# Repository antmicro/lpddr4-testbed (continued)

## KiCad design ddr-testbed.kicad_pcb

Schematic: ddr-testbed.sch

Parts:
C1, C5, C40, C41, C42: C_10u_0402; 0402-cap; MPN GRM155R60J106ME44D
C2: C_3p3_0402; 0402-res; MPN C0402C339C5GACAUTO
C3: C_10n_0402; 0402-cap; MPN 04025G103ZAT2A
C4: C_100n_0402_6V3; 0402-cap; MPN 0402X104K6R3CT
C6, C7, C44, C46, C48, C50: C_1u_0201; 0201-res; MPN CC0201KRX5R5BB105
C8, C9, C10, C11, C12, C13, C14, C15, C16, C17, C18, C19, C20, C21, C22, C23, C24, C25, C26, C27, C28, C29, C30, C31, C32, C33, C34, C35, C36, C37, C38, C39, C43, C45, C47, C49, C51, C52, C53, C54, C55, C56: C_100n_0201; 0201-res; MPN CC0201KRX6S5BB104
FB1: BLM15PD121SN1D; 0402-res; MPN BLM15PD121SN1D
J1: ddr4-sodimm-edge-connector; SODIMM_DDR4_EDGE
R1: R_240R_0402; 0402-res; MPN ERJ2GEJ241X
R2: R_10k_0402; 0402-res; MPN CRCW040210K0FKEDHP
R4, R5, R11, R12, R27, R28, R29, R31, R36: R_0R_0402; 0402-res; MPN ERJ2GE0R00X
R6, R7, R8, R9, R13, R14, R15, R16, R17, R18, R19, R20, R21, R22, R23, R24, R25, R26, R30, R32, R37: R_40R2_0402; 0402-res; MPN MCWR04X40R2FTL
R10: R_75R_0402; 0402-res; MPN RC0402FR-0775RL
R33, R34: R_80R6_0402; 0402-res; MPN MC00625W0402180R6
R35: R_4k7_0402; 0402-res; MPN ERJ2GEJ472X
U1: MT53E256M16D1; BGA-200_10.0x14.5mm_Layout12x22_P0.80x0.65mm

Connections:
/ACT_N: J1.114
/ALERT_N: J1.116, R37.1
/BA0: J1.150
/BA1: J1.145
/BG0: J1.113
/BG1: J1.115
/CA0_A: J1.144, R13.1, U1.H2 (CA0_A)
/CA0_B: J1.146, R20.1, U1.R2 (CA0_B)
/CA1_A: J1.133, R14.1, U1.J2 (CA1_A)
/CA1_B: J1.120, R21.1, U1.P2 (CA1_B)
/CA2_A: J1.132, R15.1, U1.H9 (CA2_A)
/CA2_B: J1.119, R22.1, U1.R9 (CA2_B)
/CA3_A: J1.131, R16.1, U1.H10 (CA3_A)
/CA3_B: J1.158, R23.1, U1.R10 (CA3_B)
/CA4_A: J1.128, R17.1, U1.H11 (CA4_A)
/CA4_B: J1.151, R24.1, U1.R11 (CA4_B)
/CA5_A: J1.126, R18.1, U1.J11 (CA5_A)
/CA5_B: J1.156, R25.1, U1.P11 (CA5_B)
/CK0_C: C2.1, J1.139, R7.1, U1.J9 (CK_C_A)
/CK0_T: C2.2, J1.137, R6.1, U1.J8 (CK_T_A)
/CK1_C: J1.140, R9.1, R10.2, U1.P9 (CK_C_B)
/CK1_T: J1.138, R8.1, R10.1, U1.P8 (CK_T_B)
/CKE0_A: R19.1, U1.J4 (CKE0_A)
/CKE0_B: R26.1, U1.P4 (CKE0_B)
/CKE_0: J1.109, R11.2, R31.1, R34.2
/CKE_0_A: R11.1
/CKE_0_B: R12.1
/CKE_1: J1.110, R12.2, R31.2, R33.2
/CS0_N: J1.149
/CS0_N_A: R4.1, U1.H4 (CS0_A)
/CS0_N_B: R5.1, U1.R4 (CS0_B)
/CS_0_N: R4.2, R27.1, R30.1
/CS_1_N: J1.157, R5.2, R27.2, R32.1
/DM0_N: J1.12, U1.C3 (DMI0_A)
/DM1_N: J1.33, U1.C10 (DMI1_A)
/DM2_N: J1.54, U1.Y3 (DMI0_B)
/DM3_N: J1.75, U1.Y10 (DMI1_B)
/DQ00: J1.8, U1.B2 (DQ0_A)
/DQ01: J1.7, U1.C2 (DQ1_A)
/DQ02: J1.20, U1.E2 (DQ2_A)
/DQ03: J1.21, U1.F2 (DQ3_A)
/DQ04: J1.4, U1.F4 (DQ4_A)
/DQ05: J1.3, U1.E4 (DQ5_A)
/DQ06: J1.16, U1.C4 (DQ6_A)
/DQ07: J1.17, U1.B4 (DQ7_A)
/DQ08: J1.28, U1.B11 (DQ8_A)
/DQ09: J1.29, U1.C11 (DQ9_A)
/DQ10: J1.41, U1.E11 (DQ10_A)
/DQ11: J1.42, U1.F11 (DQ11_A)
/DQ12: J1.24, U1.F9 (DQ12_A)
/DQ13: J1.25, U1.E9 (DQ13_A)
/DQ14: J1.38, U1.C9 (DQ14_A)
/DQ15: J1.37, U1.B9 (DQ15_A)
/DQ16: J1.50, U1.AA2 (DQ0_B)
/DQ17: J1.49, U1.Y2 (DQ1_B)
/DQ18: J1.62, U1.V2 (DQ2_B)
/DQ19: J1.63, U1.U2 (DQ3_B)
/DQ20: J1.46, U1.U4 (DQ4_B)
/DQ21: J1.45, U1.V4 (DQ5_B)
/DQ22: J1.58, U1.Y4 (DQ6_B)
/DQ23: J1.59, U1.AA4 (DQ7_B)
/DQ24: J1.70, U1.AA11 (DQ8_B)
/DQ25: J1.71, U1.Y11 (DQ9_B)
/DQ26: J1.83, U1.V11 (DQ10_B)
/DQ27: J1.84, U1.U11 (DQ11_B)
/DQ28: J1.66, U1.U9 (DQ12_B)
/DQ29: J1.67, U1.V9 (DQ13_B)
/DQ30: J1.79, U1.Y9 (DQ14_B)
/DQ31: J1.80, U1.AA9 (DQ15_B)
/DQS0_C: J1.11, U1.E3 (DQS0_C_A)
/DQS0_T: J1.13, U1.D3 (DQS0_T_A)
/DQS1_C: J1.32, U1.E10 (DQS1_C_A)
/DQS1_T: J1.34, U1.D10 (DQS1_T_A)
/DQS2_C: J1.53, U1.V3 (DQS0_C_B)
/DQS2_T: J1.55, U1.W3 (DQS0_T_B)
/DQS3_C: J1.74, U1.V10 (DQS1_C_B)
/DQS3_T: J1.76, U1.W10 (DQS1_T_B)
/EVENT_N: J1.134
/MEMRST_N: R36.2, U1.T11 (RESET_N)
/ODT0: J1.155, R28.2
/ODT0_A: R2.2, R28.1, U1.G2 (ODT_CA_A)
/ODT0_B: R29.1, U1.T2 (ODT_CA_B)
/ODT1: J1.161, R29.2
/PARITY: J1.143
/RESET_CONN_N: J1.108, R35.1, R36.1
/SA0: J1.256
/SA1: J1.166, J1.260
/SCL: J1.253
/SDA: J1.254
/VREFCA: C4.1, J1.164
DDRVCC: C3.1, C4.2, R37.2
GND: C1.2, C3.2, C5.2, C6.2, C7.2, C8.2, C9.2, C10.2, C11.2, C12.2, C13.2, C14.2, C15.2, C16.2, C17.2, C18.2, C19.2, C20.2, C21.2, C22.2, C23.2, C24.2, C25.2, C26.2, C27.2, C28.2, C29.2, C30.2, C31.2, C32.2, C33.2, C34.2, C35.2, C36.2, C37.2, C38.2, C39.2, C40.2, C41.2, C42.2, C43.2, C44.2, C45.2, C46.2, C47.2, C48.2, C49.2, C50.2, C51.2, C52.2, C53.2, C54.2, C55.2, C56.2, J1.1, J1.2, J1.5, J1.6, J1.9, J1.10, J1.14, J1.15, J1.18, J1.19, J1.22, J1.23, J1.26, J1.27, J1.30, J1.31, J1.35, J1.36, J1.39, J1.40, J1.43, J1.44, J1.47, J1.48, J1.51, J1.52, J1.56, J1.57, J1.60, J1.61, J1.64, J1.65, J1.68, J1.69, J1.72, J1.73, J1.77, J1.78, J1.81, J1.82, J1.85, J1.86, J1.89, J1.90, J1.93, J1.94, J1.98, J1.99, J1.102, J1.103, J1.106, J1.107, J1.167, J1.168, J1.171, J1.172, J1.175, J1.176, J1.180, J1.181, J1.184, J1.185, J1.188, J1.189, J1.192, J1.193, J1.196, J1.197, J1.201, J1.202, J1.205, J1.206, J1.209, J1.210, J1.213, J1.214, J1.217, J1.218, J1.222, J1.223, J1.226, J1.227, J1.230, J1.231, J1.234, J1.235, J1.238, J1.239, J1.243, J1.244, J1.247, J1.248, J1.251, J1.252, R6.2, R7.2, R8.2, R9.2, R13.2, R14.2, R15.2, R16.2, R17.2, R18.2, R19.2, R20.2, R21.2, R22.2, R23.2, R24.2, R25.2, R26.2, R30.2, R32.2, R35.2, U1.A3 (VSS), U1.A10 (VSS), U1.AB3 (VSS), U1.AB5 (VSS), U1.AB8 (VSS), U1.AB10 (VSS), U1.C1 (VSS), U1.C5 (VSS), U1.C8 (VSS), U1.C12 (VSS), U1.D2 (VSS), U1.D4 (VSS), U1.D9 (VSS), U1.D11 (VSS), U1.E1 (VSS), U1.E5 (VSS), U1.E8 (VSS), U1.E12 (VSS), U1.G1 (VSS), U1.G3 (VSS), U1.G5 (VSS), U1.G8 (VSS), U1.G10 (VSS), U1.G12 (VSS), U1.J1 (VSS), U1.J3 (VSS), U1.J10 (VSS), U1.J12 (VSS), U1.K2 (VSS), U1.K4 (VSS), U1.K9 (VSS), U1.K11 (VSS), U1.N2 (VSS), U1.N4 (VSS), U1.N9 (VSS), U1.N11 (VSS), U1.P1 (VSS), U1.P3 (VSS), U1.P10 (VSS), U1.P12 (VSS), U1.T1 (VSS), U1.T3 (VSS), U1.T5 (VSS), U1.T8 (VSS), U1.T10 (VSS), U1.T12 (VSS), U1.V1 (VSS), U1.V5 (VSS), U1.V8 (VSS), U1.V12 (VSS), U1.W2 (VSS), U1.W4 (VSS), U1.W9 (VSS), U1.W11 (VSS), U1.Y1 (VSS), U1.Y5 (VSS), U1.Y8 (VSS), U1.Y12 (VSS)
unnamed: R1.1, U1.A5 (ZQ0)
VDD1: C41.1, C43.1, C45.1, C47.1, C49.1, C51.1, C52.1, C54.1, C56.1, FB1.1, U1.F1 (VDD1), U1.F12 (VDD1), U1.G4 (VDD1), U1.G9 (VDD1), U1.T4 (VDD1), U1.T9 (VDD1), U1.U1 (VDD1), U1.U12 (VDD1)
VDD1_A: FB1.2, J1.123, J1.124, J1.129, J1.130
VDD2: C1.1, C6.1, C8.1, C10.1, C12.1, C14.1, C16.1, C18.1, C20.1, C22.1, C24.1, C26.1, C28.1, C30.1, C32.1, C34.1, C36.1, C38.1, C40.1, C42.1, C44.1, C46.1, C48.1, C50.1, C53.1, C55.1, J1.135, J1.136, J1.141, J1.142, J1.147, J1.148, J1.153, J1.154, J1.159, J1.160, J1.163, U1.A4 (VDD2), U1.A9 (VDD2), U1.AB4 (VDD2), U1.AB9 (VDD2), U1.F5 (VDD2), U1.F8 (VDD2), U1.H1 (VDD2), U1.H5 (VDD2), U1.H8 (VDD2), U1.H12 (VDD2), U1.K1 (VDD2), U1.K3 (VDD2), U1.K10 (VDD2), U1.K12 (VDD2), U1.N1 (VDD2), U1.N3 (VDD2), U1.N10 (VDD2), U1.N12 (VDD2), U1.R1 (VDD2), U1.R5 (VDD2), U1.R8 (VDD2), U1.R12 (VDD2), U1.U5 (VDD2), U1.U8 (VDD2)
VDDQ: C5.1, C7.1, C9.1, C11.1, C13.1, C15.1, C17.1, C19.1, C21.1, C23.1, C25.1, C27.1, C29.1, C31.1, C33.1, C35.1, C37.1, C39.1, J1.111, J1.112, J1.117, J1.118, R1.2, R2.1, R33.1, R34.1, U1.AA3 (VDDQ), U1.AA5 (VDDQ), U1.AA8 (VDDQ), U1.AA10 (VDDQ), U1.B3 (VDDQ), U1.B5 (VDDQ), U1.B8 (VDDQ), U1.B10 (VDDQ), U1.D1 (VDDQ), U1.D5 (VDDQ), U1.D8 (VDDQ), U1.D12 (VDDQ), U1.F3 (VDDQ), U1.F10 (VDDQ), U1.U3 (VDDQ), U1.U10 (VDDQ), U1.W1 (VDDQ), U1.W5 (VDDQ), U1.W8 (VDDQ), U1.W12 (VDDQ)
VDDSPD: J1.255
VPP: J1.257, J1.259
VTT: J1.258

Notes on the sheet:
Connector
Single LPDDR4 die
LPDDR4
Second LPDDR4 die
What is taht pin?
Bank adress
Bank group
To check
What is this resistor for?
Pull up or pull down?
DDR4
Power filtering

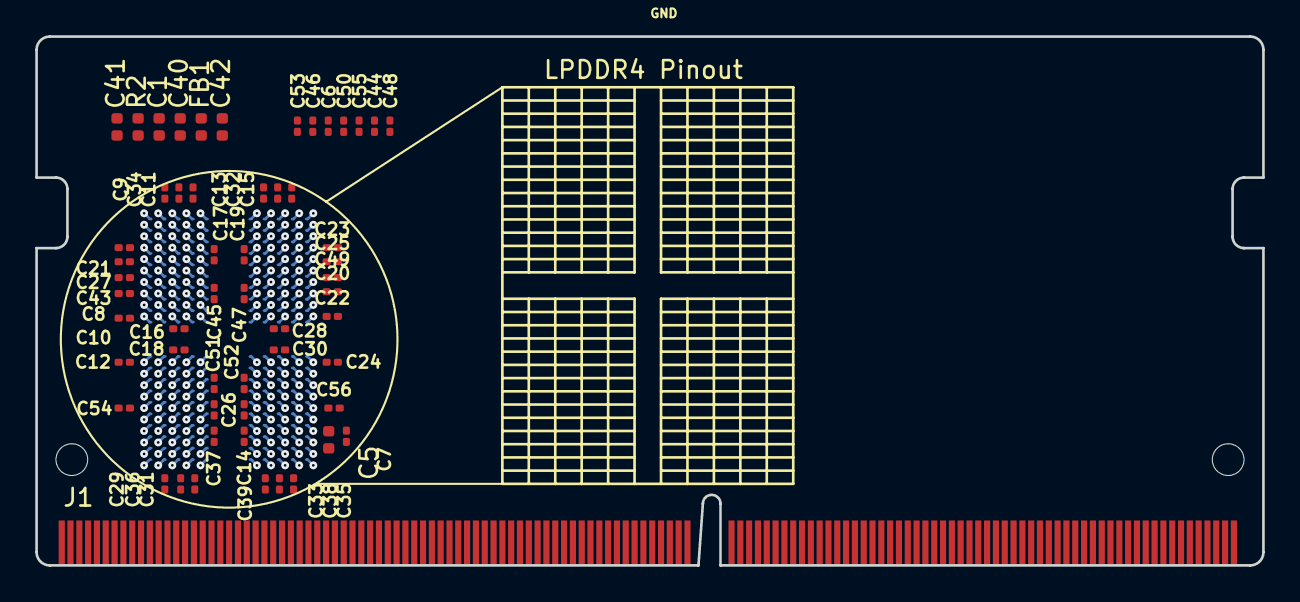
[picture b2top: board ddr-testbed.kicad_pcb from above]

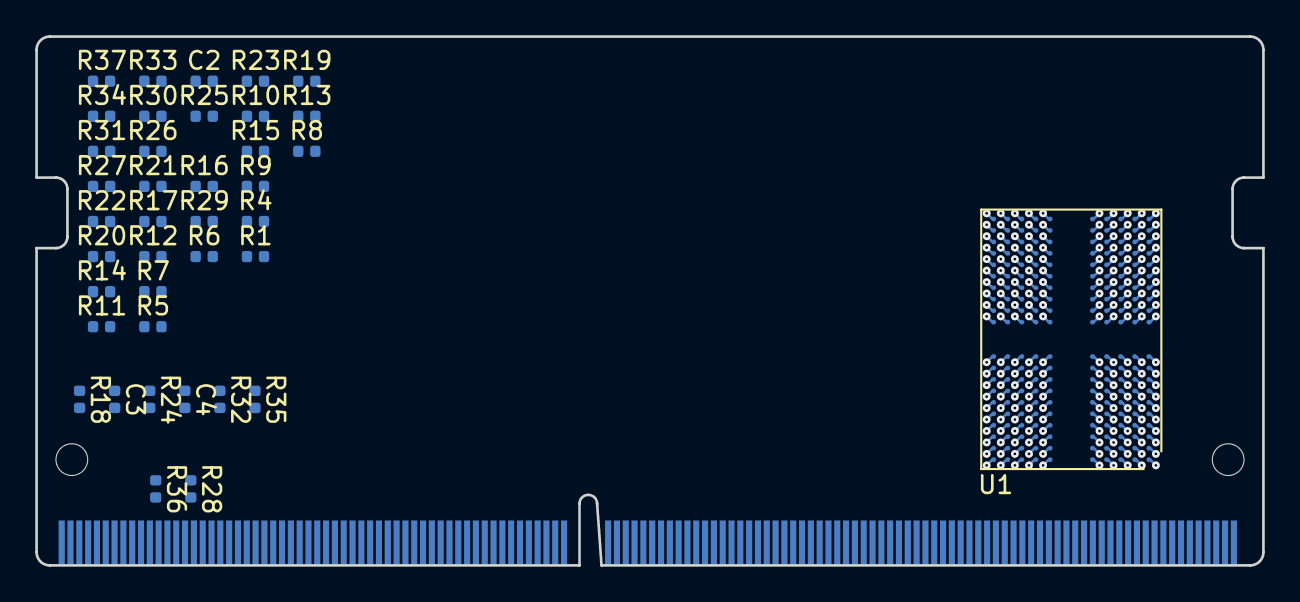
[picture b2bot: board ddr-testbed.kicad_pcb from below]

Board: 4 copper layers, 69.6 x 30.0 mm, 95 parts (39 on the bottom side), 85 nets.

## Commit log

2020-11-02 Add schamatic sheet
2020-12-10 Added edge connector escape
2020-12-10 Change labels to global
2020-12-10 Routing of all high speed DDR signals done
2020-12-10 LPDDR4 escape done, replaced DDR3 edge connector (requires connecting)
2020-12-10 Redesign power supply and filtering WIP
2020-12-10 Add data resistors sheet
2020-12-10 Update file structure
2020-12-10 Add changes in pull ups and add missing components
2020-12-10 Add changes refering to Xilinx documentation
2020-12-10 Remove data resistors sheet and add notes
2020-12-10 Preliminary LPDDR4 escape layout
2020-12-10 Passive components update, edge connector routing wip
2020-12-10 Add LICENSE
2020-12-10 Add basic PCB outline
2020-12-10 Updated LPDDR4 connection on edge connector (supplies to be added)
2020-12-10 Fix outline_v2
2020-12-10 Add initial component placement
2020-12-10 Add changes around CKE pins and some notes
2020-12-10 Add power filtering sheet
2020-12-10 Add LPDDR4 Fanout and pinout tabele
2020-12-10 Fix outline
2020-12-10 Replace capacitors and place them on PCB
2020-12-10 Add double die configuration
2020-12-10 Connect power supply to SO-DIMM connector
2020-12-10 Temporarily move filtering caps
2020-12-10 Introduce schematic sheets
2020-12-10 Update edge connector
2020-12-10 Connect power supplies and CHANNEL A signals to edge connector
2020-12-10 Connect signals to DDR CHANNEL A
2020-12-10 Update board setup for 6L
2020-12-10 Reverse connections of DQ4_A ... DQ0_A
2020-12-10 Connect CA and DQ signals
2020-12-10 Add tune DQ length
2020-12-10 Equalize CA lanes
2020-12-10 Add vias for power distribution
2020-12-10 Add intitial README
2020-12-13 Remove obsolete RC components around CK and CE signals
2020-12-13 Cleanup, add TODOs
2020-12-14 Add filtering caps to VDDQ
2020-12-14 Add Filtering to VCC1
2020-12-14 Add filtering to VDD1
2020-12-14 Route power planes
2020-12-14 Fully routed, DRC clean
2021-01-13 Reconnect RESET_N and ODT_CA to IO_P4 and IO_N5
2021-01-13 Remove note
2021-01-13 Update references
2021-01-13 Add OSHW logotype
2021-01-13 Optimize pairs of buried vias
2021-01-13 Update local libs, resolve DRC
2021-01-13 Remove redundant sheet
2021-01-13 Release 1.0.0 uploaded to CH
2021-01-13 Update 3DVis
2021-03-12 Add photo
2021-03-12 Update LICENSE
2021-03-12 README: update design status
2021-04-01 Update DRAM MPN
2021-04-02 Added sheet for EEPROM/LEDs
2021-04-07 Added EEPROM and LED circuits to schematic
2021-04-07 Component placement for EEPROM/LEDs
2021-04-22 Changed DDR type to MT53E1G32D2NP-046 WT:A
2021-04-22 Add eeprom routing
2021-04-22 Update schematics
2021-05-06 Bump revision to 1.1.0
2021-05-20 Bumped rev on PCB
2021-06-24 Notes added by 'git notes add'
2021-07-02 Replace broken component -PCA6408APW
2022-05-27 resize image
2022-06-03 Convert README to .md, added badge
2022-06-03 Corrected badge
2022-12-28 Migrate to KiCad 6
2022-12-28 Clean DRC
2022-12-28 Replace burried vias with regular vias
2022-12-29 Fix net names
2022-12-29 Length matching
2022-12-29 Bump revision to 1.2.0
2022-12-30 Update ignore
2022-12-30 Update signage
2022-12-30 Update schematic
2023-03-30 README: update the licensing string
2023-05-30 [#45231] globlib
2023-05-30 Fix missing global links (wip), designators fixed
2023-05-31 Fix missing global links
2023-10-13 Introduce component standardization
2023-10-13 Cleanup
2023-10-16 Add OHP assets, stop ignoring csv
2024-03-25 [#56947] Correct component references
2024-03-25 Upload assets
2024-03-26 [#56947] Fix missing highlights in OHP
2024-03-26 [#56947] Loclib
2024-03-26 [#56947] Bump revision & date
2024-03-27 Update assets
2024-03-29 [#56947] Removed KiCAD 5 files
2024-03-29 [#56947] Cleaned DRC
2025-11-05 [#86301] Project refresh 81589
